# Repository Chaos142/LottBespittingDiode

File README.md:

# Lott-Bespitting Diode (LBD)

A high-intensity IR blaster built on the RP2040. Browser-native control over WebSerial, MOSFET-driven IR output, 38kHz NEC modulation. Fully open source.

[Home Page](https://chaowoses.github.io/LottBespittingDiode/) &middot; [Controller](https://chaowoses.github.io/LottBespittingDiode/controller.html)

Named for Mrs. Lott, the worst teacher I ever had, and her classroom projector.

---

## Features

- **Web Controller**: Full single-page app to manage IR remotes, browse the Flipper-IRDB, compose NEC signals, and transmit over WebSerial
- **In-Browser Schematic Viewer**: Browse all hardware schematics directly on the landing page via KiCanvas
- **Auto-Generated BOM**: Bill of materials extracted from KiCad schematics and embedded in the landing page, updated on every push
- **IRDB Integration**: Browse and import from [Lucaslhm/Flipper-IRDB](https://github.com/Lucaslhm/Flipper-IRDB) directly from the controller
- **NEC Protocol Engine**: CircuitPython firmware with hardware-timed 38kHz carrier modulation
- **Library Management**: Organize remotes and signals in folders with drag-and-drop, favorites, and inline editing

---

## Project Structure

```
app/                  # Web front-end
  index.html          # Landing page (hero, BOM, schematic viewer, docs)
  index.css           # Landing page styles (dark theme, purple/amber)
  index.js            # Landing page interactivity (tabs, viewer)
  controller.html     # WebSerial controller app
  style.css           # Controller styles
  script.js           # Controller logic (serial, library, IRDB, transmit)
  three-scene.js      # Three.js particle background

firmware/             # CircuitPython firmware
  code.py             # NEC protocol engine over USB serial
  lib/                # Runtime libraries

hardware/             # KiCad hardware design
  LBD.kicad_sch       # Main schematic (RP2040, MOSFET, IR matrix)
  power.kicad_sch     # Power regulation (TPSM828214SILR)
  flash.kicad_sch     # External flash (W25Q128)
  usb.kicad_sch       # USB-C (USB4155)
  prototype/prototype.kicad_sch # Breadboard/perfboard prototype variant
  LBD.kicad_pcb       # PCB layout

scripts/              # Utility scripts
  generate_bom.py     # Auto-generates BOM HTML from KiCad schematics
  ir_tester.py        # Standalone IR transmission test
```

---

## Hardware

> The embedded PCB design isn't finalized yet. Build the prototype on a breadboard or perfboard using the [prototype schematic](hardware/prototype.kicad_sch).

The full design targets a custom PCB with an RP2040, MOSFET-switched IR LED array, USB-C, and external flash. Five KiCad schematics cover the main board, power regulation, flash memory, USB connector, and a simplified prototype variant.

---

## Firmware

The [CircuitPython firmware](firmware/code.py) implements a standard NEC protocol engine:

- 38kHz carrier modulation via `pulseio.PulseOut`
- Listens for 4-byte NEC arrays over USB serial
- Drives a status LED and the IR output on GPIO
- Header: 9000&micro;s mark / 4500&micro;s space
- Bit coding: 560&micro;s mark + 1690&micro;s (1) or 560&micro;s (0)
- Compatible with any NEC IR receiver

```python
import time
import board
import pwmio

# 38kHz carrier wave initialization
ir_pwm = pwmio.PWMOut(board.GP16, frequency=38000, duty_cycle=0)

def pulse_nec(mark_us, space_us):
    # Enable carrier wave modulation for duration of mark
    ir_pwm.duty_cycle = 32768  # 50% duty cycle
    time.sleep_us(mark_us)

    # Disable carrier wave modulation for duration of space
    ir_pwm.duty_cycle = 0
    time.sleep_us(space_us)
```

---

## Web Interface

Two pages are served via GitHub Pages:

| Page | Description |
|---|---|
| **Landing Page** (`index.html`) | Project overview, BOM table, KiCanvas schematic viewer, architecture docs, features, setup guide |
| **Controller** (`controller.html`) | Full WebSerial-based remote control app with library management, IRDB browser, signal composer, and transmit history |

---

## Setup & Flash

> Build the prototype on a breadboard or perfboard using the [prototype schematic](hardware/prototype.kicad_sch).

<details>
<summary><strong>DIY / Prototype Only</strong>: Steps 1 and 2 (skip if you have a pre-assembled unit)</summary>

### Step 1: Enter Bootloader Mode

Press and hold the **BOOT** button on the board, then connect it to your computer via a data-capable USB cable. Release the button once the drive mounts.

### Step 2: Install CircuitPython

A mass storage volume named `RPI-RP2` will appear. Drag and drop the appropriate CircuitPython `.uf2` payload onto its root directory. The board will automatically reboot and remount as `CIRCUITPY`.

</details>

### Step 3: Deploy Firmware

Copy the contents of `firmware/` onto the `CIRCUITPY` volume root:

- `code.py`
- `lib/`

### Step 4: Plug It In & Open the Controller

Keep the device connected via USB, then open the [web controller](https://chaowoses.github.io/LottBespittingDiode/controller.html) in a Chromium-based browser. Click **Connect** to establish the WebSerial session.

To run locally (required for development):

```bash
git clone https://github.com/chaowoses/LottBespittingDiode.git
cd LottBespittingDiode
python -m http.server 8080
# open http://localhost:8080
```

---

## License & Terms of Use

> [!CAUTION]
> **STRICTLY PROHIBITED FOR ILLEGAL USE**
>
> This project is designed solely for personal engineering research, hardware prototyping, and authorized testing.
> You may only operate this device on equipment you personally own or have explicit permission to control.
> The creator assumes no liability for misuse, property disruption, or equipment damage.

This project (software, firmware, schematics, PCB layouts, and documentation) is licensed under the **GNU General Public License v3.0 (GPL-3.0)**.

Copyright &copy; 2026 Josh Felder (Chaos). All Rights Reserved.

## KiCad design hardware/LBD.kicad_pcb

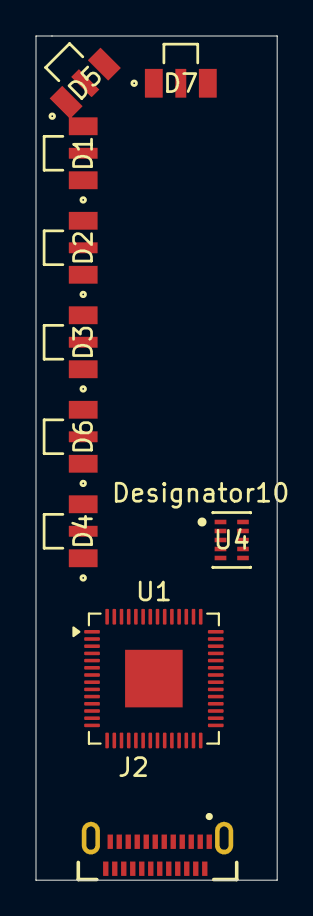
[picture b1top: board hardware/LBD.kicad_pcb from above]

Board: 2 copper layers, 13.4 x 46.9 mm, 10 parts (0 on the bottom side), 7 nets, no tracks yet.

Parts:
D1, D2, D3, D4, D5, D6, D7: LED; LED_IN-S12_INL
J2: USB4155-03-C_REVA; GCT_USB4155-03-C_REVA
U1: RP2040; QFN-56-1EP_7x7mm_P0.4mm_EP3.2x3.2mm
U4: TPSM828214SILR

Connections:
+1V1: U1.23 (DVDD), U1.45 (VREG_VOUT), U1.50 (DVDD)
+3.3V: U1.1 (IOVDD), U1.10 (IOVDD), U1.22 (IOVDD), U1.33 (IOVDD), U1.42 (IOVDD), U1.43 (ADC_AVDD), U1.44 (VREG_VIN), U1.48 (USB_VDD), U1.49 (IOVDD), U4.5 (VOUT), U4.6 (VOUT), U4.7 (VOUT), U4.8 (FB)
/Power/PG: U1.26 (RUN), U4.4 (PG)
/USB/DN: J2.A7 (DN1), J2.B7 (DN2)
/USB/DP: J2.A6 (DP1), J2.B6 (DP2)
GND: J2.A1 (GND_A), J2.A12 (GND_A__1), J2.B1 (GND_B), J2.B12 (GND_B__1), J2.S1 (SHELL_GND), J2.S2 (SHELL_GND__1), U1.19 (TESTEN), U1.57 (GND), U4.9 (GND), U4.10 (GND)
VBUS: J2.A4 (VBUS_A), J2.A9 (VBUS_A__1), J2.B4 (VBUS_B), J2.B9 (VBUS_B__1), U4.1 (VIN), U4.2 (VIN), U4.3 (EN)

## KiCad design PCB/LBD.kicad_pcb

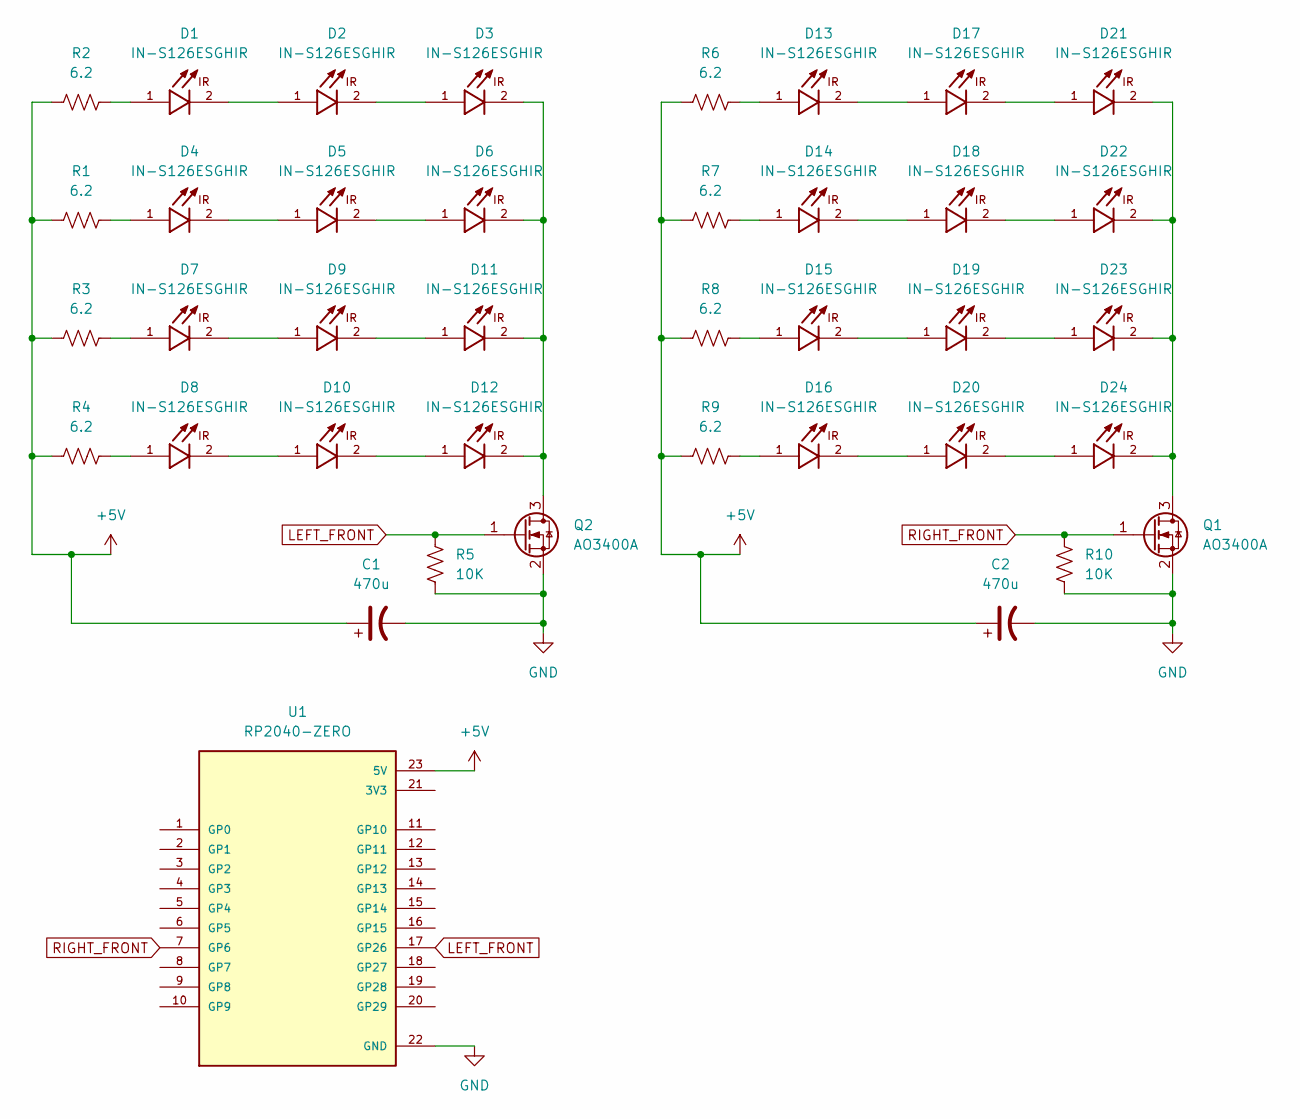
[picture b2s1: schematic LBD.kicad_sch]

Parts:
C1, C2: 470u; CP_Elec_8x10.5
D1, D2, D3, D4, D5, D6, D7, D8, D9, D10, D11, D12, D13, D14, D15, D16, D17, D18, D19, D20, D21, D22, D23, D24: IN-S126ESGHIR; LED_IN-S126ESGHIR; PARTREV 03-17-2020
Q1, Q2: AO3400A; SOT-23
R1, R2, R3, R4, R6, R7, R8, R9: 6.2; R_1206_3216Metric
R5, R10: 10K; R_0805_2012Metric
U1: RP2040-ZERO; MODULE_RP2040-ONE; PARTREV NA

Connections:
+5V: C1.1, C2.1, R1.1, R2.1, R3.1, R4.1, R6.1, R7.1, R8.1, R9.1, U1.23 (5V)
GND: C1.2, C2.2, Q1.2 (S), Q2.2 (S), R5.2, R10.2, U1.22 (GND)
LEFT_FRONT: Q2.1 (G), R5.1, U1.17 (GP26)
unnamed: D1.1, R2.2
unnamed: D1.2, D2.1
unnamed: D2.2, D3.1
unnamed: D4.1, R1.2
unnamed: D4.2, D5.1
unnamed: D5.2, D6.1
unnamed: D7.1, R3.2
unnamed: D7.2, D9.1
unnamed: D8.1, R4.2
unnamed: D8.2, D10.1
unnamed: D10.2, D12.1
unnamed: D9.2, D11.1
unnamed: D13.1, R6.2
unnamed: D13.2, D17.1
unnamed: D14.1, R7.2
unnamed: D14.2, D18.1
unnamed: D15.1, R8.2
unnamed: D15.2, D19.1
unnamed: D16.1, R9.2
unnamed: D16.2, D20.1
unnamed: D17.2, D21.1
unnamed: D18.2, D22.1
unnamed: D19.2, D23.1
unnamed: D20.2, D24.1
unnamed: D21.2, D22.2, D23.2, D24.2, Q1.3 (D)
unnamed: D3.2, D6.2, D11.2, D12.2, Q2.3 (D)
RIGHT_FRONT: Q1.1 (G), R10.1, U1.7 (GP6)

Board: 2 copper layers, 39 parts (0 on the bottom side), 30 nets, no tracks yet.

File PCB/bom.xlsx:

Designator | Description | Manufacturer | Manufacturer Part Number | Digikey Part Number | Link | Quantity | Libraries | Datasheet
 | Waveshare RP2040-Tiny | Waveshare RP2040-Tiny Development Board, Based On Official RP2040 Dual Core Pro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 |  |  | https://www.waveshare.com/rp2040-tiny.htm?srsltid=AfmBOorKS5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 | 1 | https://github.com/kohaku276/RP2040-Tiny_kicad | https://www.waveshare.com/wiki/RP2040-Tiny
 | USB-C (USB TYPE-C) USB 3.2 Gen 2 (USB 3.1 Gen 2, Superspeed + (USB 3.1)) Plug C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 | GCT | USB4155-03-C | 2073-USB4155-03-CCT-ND | https://www.digikey.com/en/products/detail/gct/USB4155-03-C/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 | 1 | https://www.digikey.com/en/models/14305161?tab=snapmagic | https://gct.co/files/specs/usb4155-spec.pdf
 | Infrared (IR) Emitter 940nm 1.46V 100mA 92mW/sr @ 100mA (Typ) 30° 1210 (3225 Me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 | Inolux | IN-S126ESGHIR | 1830-IN-S126ESGHIRCT-ND | https://www.digikey.com/en/products/detail/inolux/IN-S126ESG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 | 12 | https://www.digikey.com/en/models/10384762?tab=ultralibrarian | http://www.inolux-corp.com/datasheet/IR/Emitter/940%20nm%20S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
 | N-Channel 30 V 5.7A (Ta) 1.4W (Ta) Surface Mount SOT-23-3 | Alpha & Omega Semiconductor Inc. | AO3400A | 785-1000-1-ND | https://www.digikey.com/en/products/detail/alpha-omega-semic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 | 1 | https://www.digikey.com/en/models/1855772?tab=snapmagic | https://mm.digikey.com/Volume0/opasdata/d220001/medias/docus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
 |  |  |  | RMCF1206FT6R20CT-ND | https://www.digikey.com/en/products/detail/stackpole-electro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

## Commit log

2026-05-07 started bom
2026-05-14 bruh
2026-05-17 worked on schematic
2026-05-19 finished core, flash, crystal oscillator, and power regulation
2026-05-23 created web app and firmware v1
2026-05-23 rethemed
2026-05-24 cleaned some frontend
    to do:
    fix folder importing to actually import the folder instead of dumping the contents
    fix dragging
    add a history to the transmit tab so you can re-transmit
2026-05-26 redid ui
2026-05-29 added lock files to gitignore
2026-06-01 cleaned up schematic
2026-06-01 added pages deployment workflow
2026-06-01 fixed workflow
2026-06-01 forced redeploy
2026-06-02 added a vibecoded home page yay
2026-06-06 fixed schematic render path
2026-06-06 reorganized buttons
2026-06-06 fixed schematic rendering ... again
2026-06-06 added prototype schematic
2026-06-09 added more mobile support
2026-06-13 started placing leds
2026-06-13 Update BOM from schematics [skip ci]
2026-06-13 deploy: b420a0b439f6bc27b3d143c77f54cfc939eae909
